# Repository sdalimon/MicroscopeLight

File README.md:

# MicroscopeLight
A strap on light ring for my desk microscope

I had bought a cheap microscope that connects to a HDMI monitor or PC over USB.  It included two LED lights on the base, but I found them to not always be easy enough to aim and get enough light.  

This is a ring light that fits around the lens on the microscope.  It is held on with some wire ties to the vertical adjustment mechanism.  

Power is micro USB B.  On my setup I patched it into the USB lights on the base.

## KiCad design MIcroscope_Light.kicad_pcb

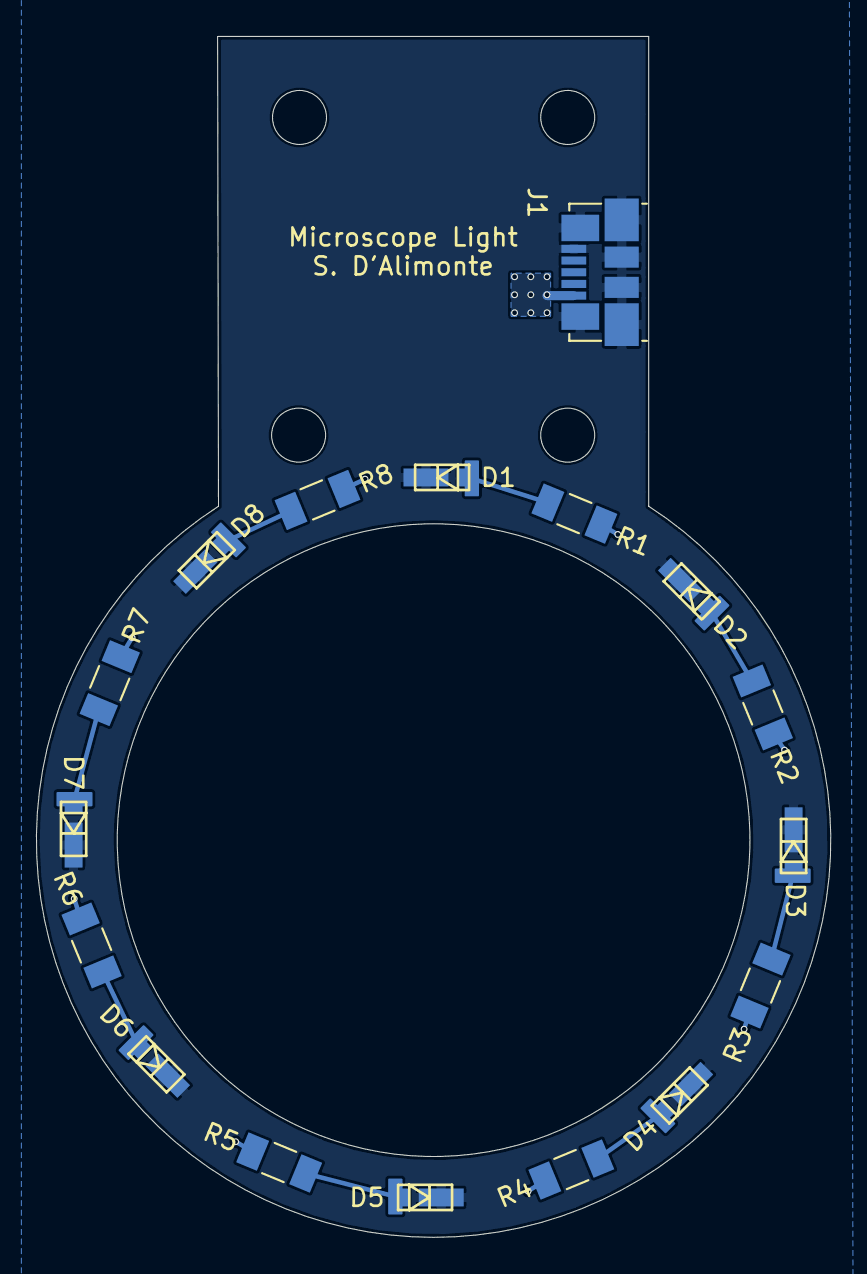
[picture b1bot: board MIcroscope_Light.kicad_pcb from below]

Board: 2 copper layers, 44.1 x 66.7 mm, 21 parts (17 on the bottom side), 10 nets.

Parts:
D1, D2, D3, D4, D5, D6, D7, D8: MP-3014-1100-27-80
J1: USB_B_Micro; USB_Micro-B_Molex_47346-0001
MK1, MK2, MK3, MK4: Mounting_Hole; MountingHole_3mm
R1, R2, R3, R4, R5, R6, R7, R8: 39; R_1206_3216Metric_Pad1.24x1.80mm_HandSolder

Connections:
+5V: J1.1, R1.1, R2.1, R3.1, R4.1, R5.1, R6.1, R7.1, R8.1
GND: D1.1, D2.1, D3.1, D4.1, D5.1, D6.1, D7.1, D8.1, J1.5, J1.6
unnamed: D1.2, R1.2
unnamed: D2.2, R2.2
unnamed: D3.2, R3.2
unnamed: D4.2, R4.2
unnamed: D5.2, R5.2
unnamed: D6.2, R6.2
unnamed: D7.2, R7.2
unnamed: D8.2, R8.2

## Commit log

2021-02-15 Add files via upload
    Upload files
2021-02-15 Update README.md
    Update README
